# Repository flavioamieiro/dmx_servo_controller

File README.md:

# dmx_servo_controller

AMIEIRO + DELED : SERVO DMX Controller V0.1

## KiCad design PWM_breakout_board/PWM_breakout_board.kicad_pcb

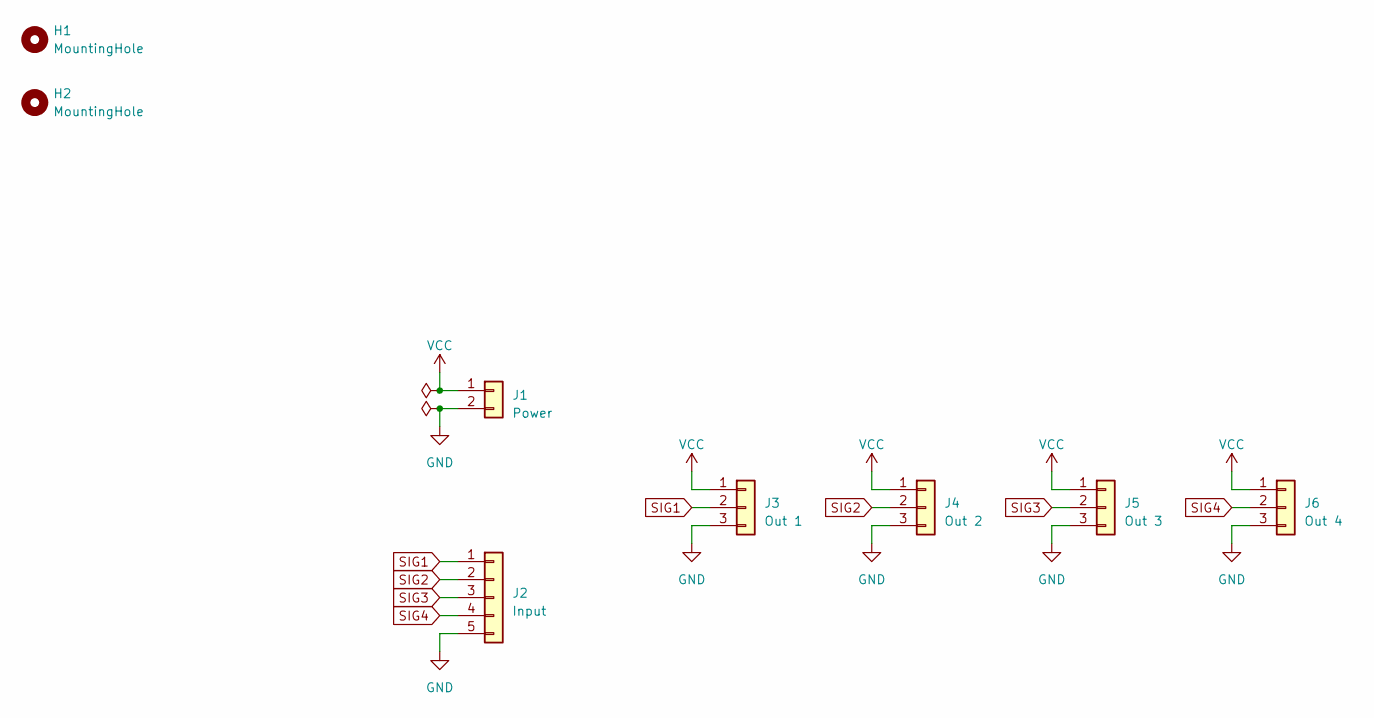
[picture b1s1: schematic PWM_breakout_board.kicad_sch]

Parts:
H1, H2: MountingHole; MountingHole_4.3mm_M4_ISO7380
J1: Power; TerminalBlock_bornier-2_P5.08mm
J2: Input; JST_XH_B5B-XH-AM_1x05_P2.50mm_Vertical
J3: Out 1; TerminalBlock_bornier-3_P5.08mm
J4: Out 2; TerminalBlock_bornier-3_P5.08mm
J5: Out 3; TerminalBlock_bornier-3_P5.08mm
J6: Out 4; TerminalBlock_bornier-3_P5.08mm

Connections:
GND: J1.2, J2.5, J3.3, J4.3, J5.3, J6.3
SIG1: J2.1, J3.2
SIG2: J2.2, J4.2
SIG3: J2.3, J5.2
SIG4: J2.4, J6.2
VCC: J1.1, J3.1, J4.1, J5.1, J6.1

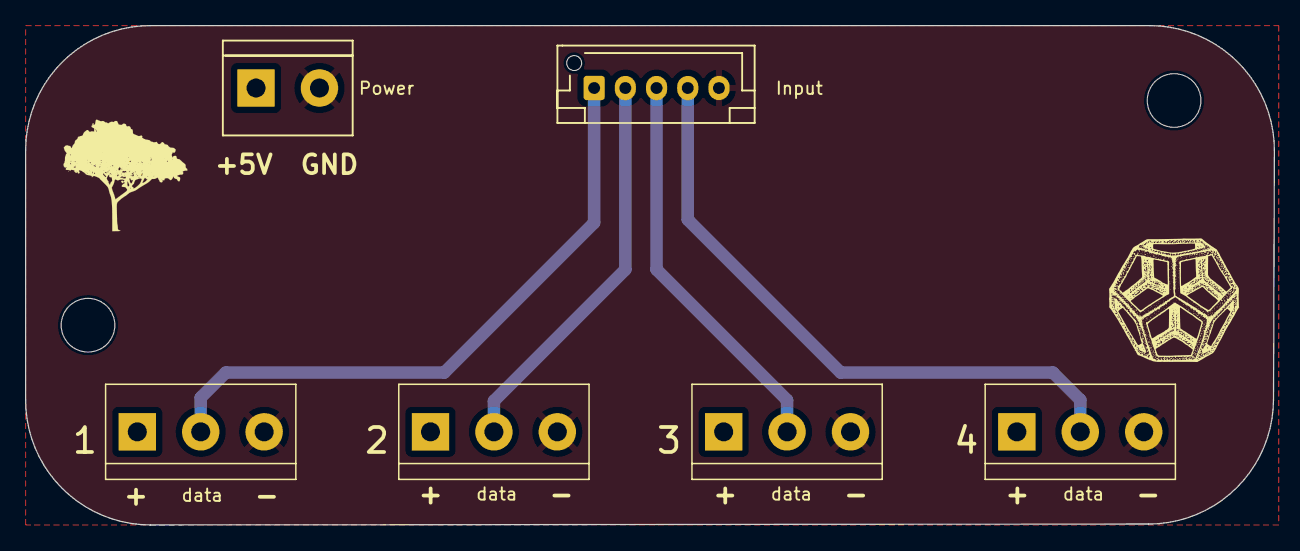
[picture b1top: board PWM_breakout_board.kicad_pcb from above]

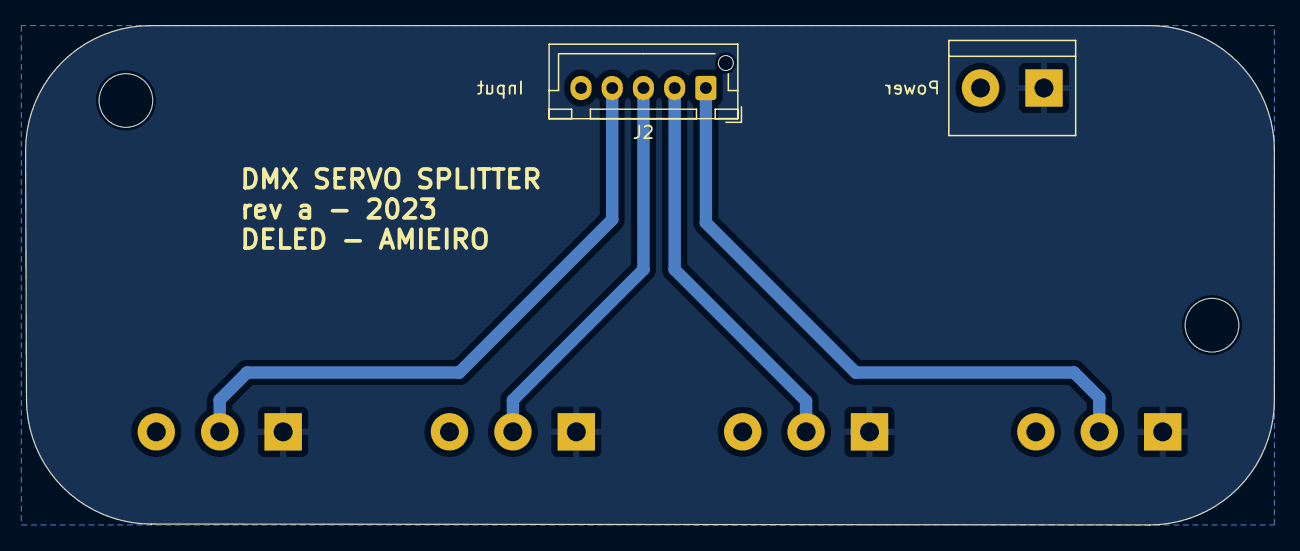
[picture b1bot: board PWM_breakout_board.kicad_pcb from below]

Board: 2 copper layers, 100.0 x 40.0 mm, 9 parts (2 on the bottom side), 6 nets.

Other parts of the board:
Ref**: Val**; ipe_logo_FSilk_10x10

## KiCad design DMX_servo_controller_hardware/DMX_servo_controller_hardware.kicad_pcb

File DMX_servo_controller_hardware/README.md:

DMX servo controller

This source describes Open Hardware and is licensed under the CERN-OHL-S v2.
You may redistribute and modify this source and make products using it under
the terms of the [CERN-OHL-S v2](https://ohwr.org/cern_ohl_s_v2.txt).

Source location: https://github.com/flavioamieiro/Neopixel-Pico-Arcade

As per CERN-OHL-S v2 section 4, should You produce hardware based on this
source, You must where practicable maintain the Source Location visible on the
external case of the Gizmo or other products you make using this source.

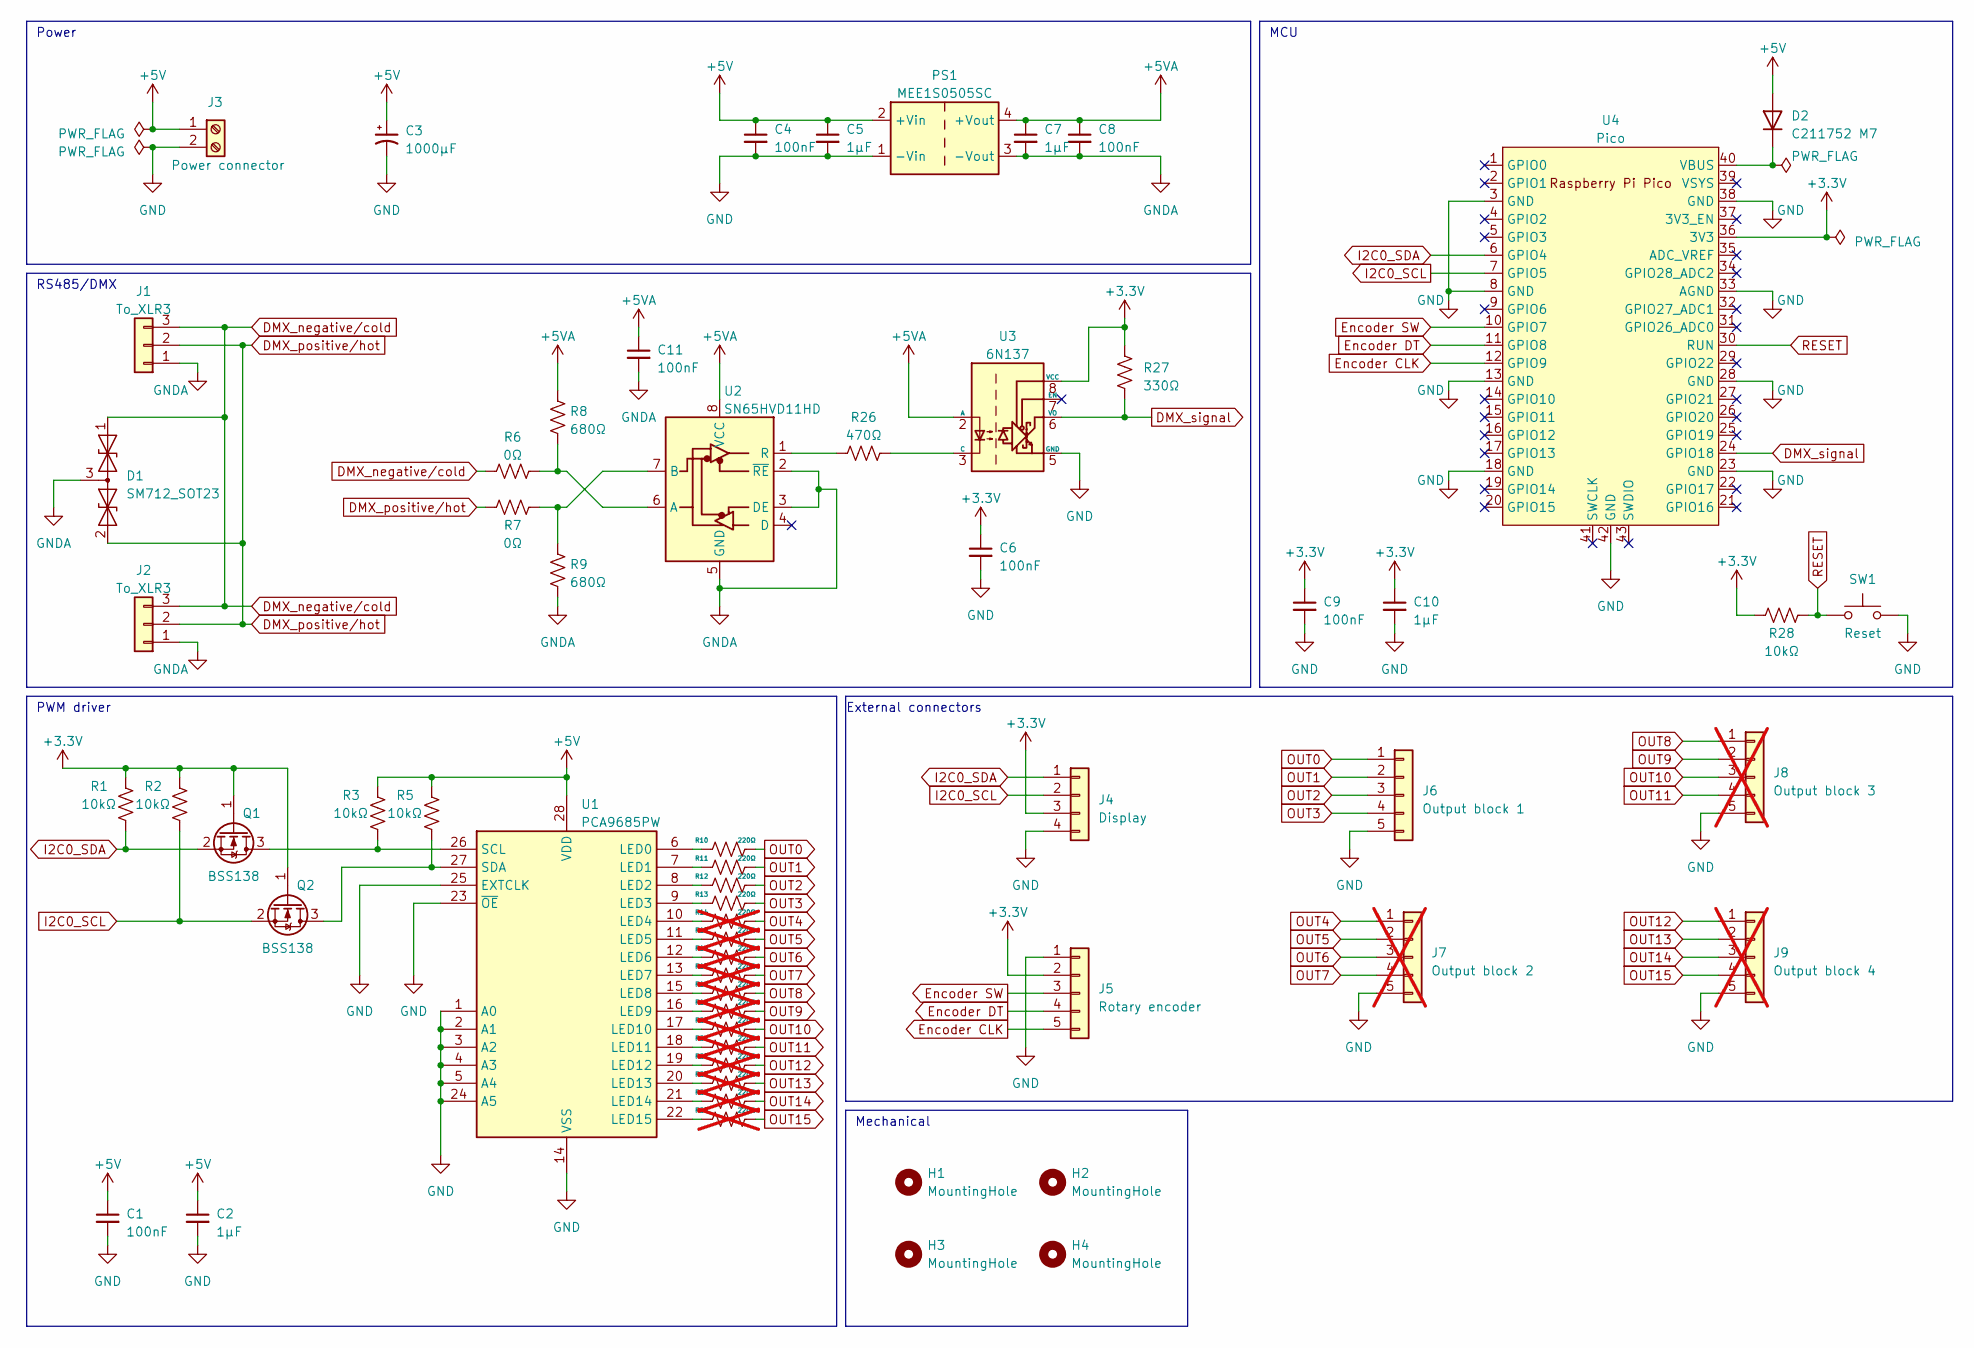
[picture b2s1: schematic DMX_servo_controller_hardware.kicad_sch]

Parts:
C1, C4, C6, C8, C9, C11: 100nF; C_0805_2012Metric_Pad1.18x1.45mm_HandSolder
C2, C5, C7, C10: 1μF; C_0805_2012Metric_Pad1.18x1.45mm_HandSolder
C3: 1000μF; CP_Radial_D10.0mm_P5.00mm
D1: SM712_SOT23; SOT-23
D2: C211752 M7; D_SMA
H1, H2, H3, H4: MountingHole; MountingHole_4.3mm_M4_ISO7380
J1, J2: To_XLR3; JST_XH_B3B-XH-AM_1x03_P2.50mm_Vertical
J3: Power connector; TerminalBlock_bornier-2_P5.08mm
J4: Display; JST_XH_B4B-XH-AM_1x04_P2.50mm_Vertical
J5: Rotary encoder; JST_XH_B5B-XH-AM_1x05_P2.50mm_Vertical
J6: Output block 1; JST_XH_B5B-XH-AM_1x05_P2.50mm_Vertical
J7: Output block 2; JST_XH_B5B-XH-AM_1x05_P2.50mm_Vertical; not fitted
J8: Output block 3; JST_XH_B5B-XH-AM_1x05_P2.50mm_Vertical; not fitted
J9: Output block 4; JST_XH_B5B-XH-AM_1x05_P2.50mm_Vertical; not fitted
PS1: MEE1S0505SC; Converter_DCDC_Murata_MEE1SxxxxSC_THT
Q1, Q2: BSS138; SOT-23
R1, R2, R3, R5, R28: 10kΩ; R_0805_2012Metric_Pad1.20x1.40mm_HandSolder
R6, R7: 0Ω; R_0805_2012Metric_Pad1.20x1.40mm_HandSolder
R8, R9: 680Ω; R_0805_2012Metric_Pad1.20x1.40mm_HandSolder
R10, R11, R12, R13: 220Ω; R_0805_2012Metric_Pad1.20x1.40mm_HandSolder
R14, R15, R16, R17, R18, R19, R20, R21, R22, R23, R24, R25: 220Ω; R_0805_2012Metric_Pad1.20x1.40mm_HandSolder; not fitted
R26: 470Ω; R_0805_2012Metric_Pad1.20x1.40mm_HandSolder
R27: 330Ω; R_0805_2012Metric_Pad1.20x1.40mm_HandSolder
SW1: Reset; SW_SPST_TL3342
U1: PCA9685PW; TSSOP-28_4.4x9.7mm_P0.65mm
U2: SN65HVD11HD; DIP-8_W7.62mm
U3: 6N137; 6N137-X007T
U4: Pico; RPi_Pico_SMD_TH

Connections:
+3.3V: C6.1, C9.1, C10.1, J4.3, J5.2, Q1.1 (G), Q2.1 (G), R1.1, R2.1, R27.1, R28.1, U3.8 (VCC), U4.36 (3V3)
+5V: C1.1, C2.1, C3.1, C4.1, C5.1, D2.2 (A), J3.1, PS1.2 (+Vin), R3.1, R5.1, U1.28 (VDD)
+5VA: C7.1, C8.1, C11.1, PS1.4 (+Vout), R8.1, U2.8 (VCC), U3.2 (A)
DMX_negative/cold: D1.1 (A1), J1.3, J2.3, R6.1
DMX_positive/hot: D1.2 (A2), J1.2, J2.2, R7.1
DMX_signal: R27.2, U3.6 (VO), U4.24 (GPIO18)
Encoder CLK: J5.5, U4.12 (GPIO9)
Encoder DT: J5.4, U4.11 (GPIO8)
Encoder SW: J5.3, U4.10 (GPIO7)
GND: C1.2, C2.2, C3.2, C4.2, C5.2, C6.2, C9.2, C10.2, J3.2, J4.4, J5.1, J6.5, J7.5, J8.5, J9.5, PS1.1 (-Vin), SW1.2, U1.1 (A0), U1.2 (A1), U1.3 (A2), U1.4 (A3), U1.5 (A4), U1.14 (VSS), U1.23 (~OE), U1.24 (A5), U1.25 (EXTCLK), U3.5 (GND), U4.3 (GND), U4.8 (GND), U4.13 (GND), U4.18 (GND), U4.23 (GND), U4.28 (GND), U4.33 (AGND), U4.38 (GND), U4.42 (GND)
GNDA: C7.2, C8.2, C11.2, D1.3 (common), J1.1, J2.1, PS1.3 (-Vout), R9.2, U2.2 (~RE), U2.3 (DE), U2.5 (GND)
I2C0_SCL: J4.2, Q2.2 (S), R2.2, U4.7 (GPIO5)
I2C0_SDA: J4.1, Q1.2 (S), R1.2, U4.6 (GPIO4)
unnamed: D2.1 (K), U4.40 (VBUS)
unnamed: Q1.3 (D), R3.2, U1.26 (SCL)
unnamed: Q2.3 (D), R5.2, U1.27 (SDA)
unnamed: R10.1, U1.6 (LED0)
unnamed: R11.1, U1.7 (LED1)
unnamed: R12.1, U1.8 (LED2)
unnamed: R13.1, U1.9 (LED3)
unnamed: R14.1, U1.10 (LED4)
unnamed: R15.1, U1.11 (LED5)
unnamed: R16.1, U1.12 (LED6)
unnamed: R17.1, U1.13 (LED7)
unnamed: R18.1, U1.15 (LED8)
unnamed: R19.1, U1.16 (LED9)
unnamed: R20.1, U1.17 (LED10)
unnamed: R21.1, U1.18 (LED11)
unnamed: R22.1, U1.19 (LED12)
unnamed: R23.1, U1.20 (LED13)
unnamed: R24.1, U1.21 (LED14)
unnamed: R25.1, U1.22 (LED15)
unnamed: R6.2, R8.2, U2.6 (A)
unnamed: R7.2, R9.1, U2.7 (B)
unnamed: R26.2, U2.1 (R)
unnamed: R26.1, U3.3 (C)
OUT0: J6.1, R10.2
OUT1: J6.2, R11.2
OUT2: J6.3, R12.2
OUT3: J6.4, R13.2
OUT4: J7.1, R14.2
OUT5: J7.2, R15.2
OUT6: J7.3, R16.2
OUT7: J7.4, R17.2
OUT8: J8.1, R18.2
OUT9: J8.2, R19.2
OUT10: J8.3, R20.2
OUT11: J8.4, R21.2
OUT12: J9.1, R22.2
OUT13: J9.2, R23.2
OUT14: J9.3, R24.2
OUT15: J9.4, R25.2
RESET: R28.2, SW1.1, U4.30 (RUN)

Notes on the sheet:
External connectors
PWM driver
RS485/DMX
MCU
Power
Mechanical

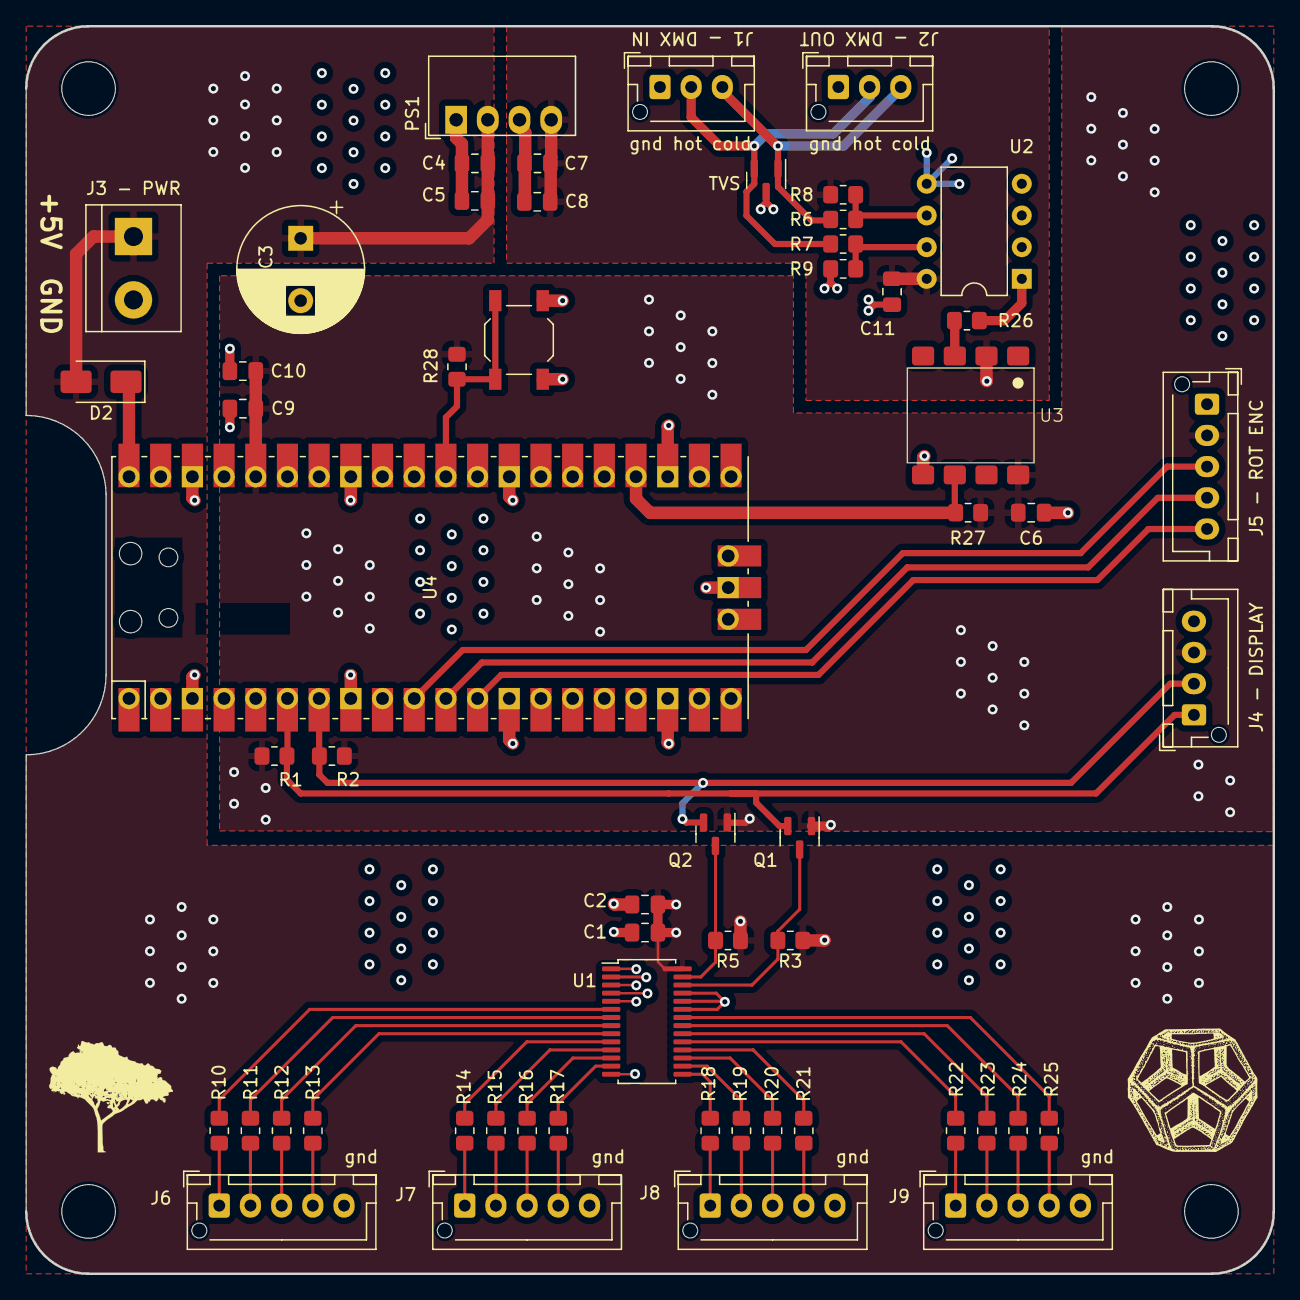
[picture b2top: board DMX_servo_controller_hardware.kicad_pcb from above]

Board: 4 copper layers, 100.0 x 100.0 mm, 62 parts (0 on the bottom side), 53 nets.

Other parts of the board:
Ref**: Val**; ipe_logo_FSilk_10x10

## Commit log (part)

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2023-03-13 Commit inicial
2023-03-13 Adiciona esquemático do protótipo de conexão do RS485
    Essa versão não tem ainda isolamento mas foi a que usamos para receber
    com sucesso mensagens DMX da mesa controladora.
2023-03-15 Adiciona código de exemplo pra ler 3 canais DMX
    Esse código funciona na IDE do Arduino usando o Arduino-pico [1]
    [1]: https://github.com/earlephilhower/arduino-pico
2023-03-15 Adiciona licença para a parte de hardware
2023-03-20 Adds Raspberry Pi pico symbol and footprint from ncarandini/KiCad-RP-Pico
    The footprint and symbol are taken from
    https://github.com/ncarandini/KiCad-RP-Pico which has a license that
    explicitly allows it to be used in projects without the same license.
    This commit also updates project files to Kicad 7.0.1
2023-03-21 Isolates DMX signal from the rest of the electronics
    We're using a 0505 5v DC/DC isolator for power and an 6N137 optocoupler
    for the signal.
    The 6N137 is supposed to work with 5V, but our tests (and other designs)
    showed that 3.3V works fine and means the optocoupler works as a level
    shifter.
2023-03-22 Moves XLR connector to a hierarchical sheet
    The XLR connectors will be in a daughter board that can be used as a
    breakout board for XLR connectors.
2023-03-22 Adds Pi Pico to the schematics
    This also adds a connector for 5V power (a screw terminal that will be
    connected to the external power supply). The 3v3 rail will come from the
    pico's regulator.
2023-03-22 Adds connections for display
    This also fixes the Reset switch (I was missing the signal on the
    push button) and adds an external connector for the XLR signal (In case
    we use the daughter board detached from the main board).
2023-03-22 WIP: Adds PCA9685 PWM driver
    This adds the IC and some minimal circuitry around it, but there's still
    work to be done here.
2023-03-29 Adds pull-up resistors to PCA9685 i2c lines
2023-03-29 Adds external connectors for the servos
2023-03-29 Fixes GND pin 38 type in the pi pico symbol
2023-03-30 FIxes ERC errors
2023-05-02 Renames example code
    Arduino prefers if the sketch is in a directory with the same name.
2023-05-03 Fixes OE and EXT_CLK pins on the PCA9685 schematics
    OE is active low, so it needs to be pulled to ground.
2023-05-03 Uses same i2c bus for display and pwm controller
    The devices have different addresses. There's no good reason for us not
    to use the same bus.
2023-05-03 First code example with most elements integrated
    For now, the code reads DMX input synchronously and sets channels 0 and
    15 to their position based on channel 1.
    Channels 2 and 3 define the min and max (respectively) duty cycle values
    for `setPWM` since at least the servos we tested on seem to not match
    the datasheet.
    The input value for all DMX channels is output on the OLED display.
2023-05-10 Allows controlling servos independently with each DMX channel
    This commit restructures the code to allow each servo to keep it's own
    state. This removes the temporary calibration channels that existed
    for debugging. A calibration wizzard should be included in the UI later.
2023-05-12 DMX_servo_controller_hardware/DMX_servo_controller_hardware-backups/ DMX_servo_controller_hardware/MCU_RaspberryPi_and_Boards.pretty/desktop.ini DMX_servo_controller_hardware/desktop.ini "Defini\303\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
2023-05-13 Powers PCA9685 from 5V rail
    With this, the PWM signal will be on the level the servos expect, since
    they will be powered with the same voltage. The i2c lines are level
    shifted since the RP2040 GPIOs are not 5V tolerant.
2023-05-13 Adds a diode to stop the USB from feeding the power supply when programming
2023-05-13 "addded datasheets and references repositories"
2023-05-13 "removed gdoc from files - added to .gitignore"
2023-05-13 "removed definições e escolhas.gdoc from repo"
2023-05-22 Adds power flag to the VUSB net after the diode
    This is necessary so the ERC will not complain about the pin do being
    driven.
2023-05-22 Adds minimal example code to interface with rotary encoder
    This uses Matthias Hertel's RotaryEncoder library[1].
    [1]: https://github.com/mathertel/RotaryEncoder
2023-05-22 Reorganizes code and fixes bug in servo update reference
    The loop function is now much easier to read and only calls specific
    functions that handle certain subsystems. Also, I don't know how to
    handle pointers.
2023-05-22 Reasigns component designators
2023-05-23 Final review of the schematics
    * Fixes SCL pull-up in PCA9685
    * Reviews pinouts
    * Adds series resistor to PWM signals
    * Adds bulk decoupling capacitor to 5V power rail
2023-05-26 Assigns footprints to some of the components
2023-05-26 Changes schematic to have only header to plug the panel mounted XLR3 connectors
    We will use panel mounted XLR connector, so we don't need the daughter
    board and the PCB XLR connectors anymore. Instead, the external ones
    will connect to the PCB via 2 JST headers.
2023-05-26 Assigns footprint for test points
    We might want to have all test points going to one connector (01x06 pin
    header) to make the layout easier in the future.
2023-05-26 Reorder JST conectors and PCA9685 outputs for completion (OCD) / added DNP in 4out8 outputs / removed unnecessary resistor for upper 8 outputs of PCA9685 testpoints
2023-05-31 Adds #autosaved_files# to .gitignore
2023-05-31 Adds footprint for reset pushbutton
    The footprint almost matches (and is definitely within tolerances) for
    the technical drawing and measurements taken from the pushbuttons to be
    used.
2023-06-01 Uses screw terminals for servo output connectors
2023-06-01 Uses DIP-8 footprint for SN65HVD12
2023-06-01 Switches symbol and footprint for diode on VUSB
    We're using the C211752[1] from yangjie, but since there's no schematic
    symbol for it, I replaced it with the MRA4003T3G since it has the same
    functionality and footprint and changed the value to reflect the correct
    part number.
    [1]: https://datasheet.lcsc.com/lcsc/1912111437_Yangzhou-Yangjie-Elec-Tech-M7_C211752.pdf
2023-06-01 Adds output for all PWM channels
    They are marked as unpopulated, but it's a good idea to route all
    outputs since we can than populate them if we want more channels.
2023-06-02 Reasigns all component designations
    Now that the schematic is closer to the final configuration we can have
    a better distribution of designators.
2023-06-02 Moves DMX input to GPIO15 on the Pico
    GPIO0 is UART_TX, which was causing issues[1].
    [1]: https://github.com/jostlowe/Pico-DMX/issues/26#issuecomment-1573000484
2023-06-02 Reads DMX messages asynchronously
    This way, we don't need to block until a message is sent, so we can
    process input from the rotary encoder even if no controller is sending
    data to the DMX bus.
2023-06-02 Removes minimum delay between servo moves
    Even though we're reading DMX input asynchronously, we're still only
    processing the data once per loop. Our code is already complex enough
    that by the time we loop through again we're already past the threshold
    we were setting.
2023-06-05 Changes PWM output connectors
    The outputs will be broken out into a JST connector (with ground) in
    blocks of 4 that can then be brought to the connectors to be used by the
    end-user. This is a more flexible design, as we can have the break-out
    board placed in a better place in the enclosure and also permits power
    to be delivered directly to the breakout board.
2023-06-05 Assigns footprints to symbols in PWM breakout board schematics
2023-06-05 Adds first draft of breakout board PCB mechanical design
    This is a very rough sketch for now.
2023-06-05 Uses similar 3D model for terminal blocks in the breakout board
    The Phoenix connectors are very similar to ours and the 3d models don't
    have any major impact, so we can use them since the bornier symbols
    don't have one.
2023-06-05 Roughly routes PWM breakout board as a first draft
2023-06-05 Updates PCBnew file
2023-06-05 Fixes 3d model path for PI Pico footprint
2023-06-06 Fixes footprints for resistors in the main schematics
2023-06-06 Sets main board PCB as 4 layers and set some defaults
2023-06-06 Adds four M4 mounting holes to main board
2023-06-06 Fixes decoupling in PCA9685
    When changing the power supply for the IC, I forgot to change the
    decoupling caps.
2023-06-06 Regroups components in PCB
    This is still far from a final positioning, but the groups are more
    coherent now.
2023-06-15 Switches display code to use SSD1306 OLEDs
    The displays we sourced use this controller. Since the code to actually
    interact with the display uses the Adafruit GFX library, the replacement
    is almost drop-in.
2023-07-02 First draft routing of the DMX section of the PCB
    This is far from the final layout, but it might help to start
    visualizing things.
2023-07-02 Repositions rest of the components to route them in an easier way
2023-07-02 Moves DMX signal input to GPIO18
    This will make it much easier to route the board.
2023-07-03 Reassigns pins in the code to match schematics
2023-07-03 First draft route for everything that was unrouted
    There's definitely a lot to improve still, but all nets are connected.
2023-07-14 Edits some of the silkscreen an adjusts positioning slightly
2023-07-14 Reorganizes component positioning/layout
    The connectors are now all close to the edge o the board and grouped by
    function.
    The space between components in the DMX and uC sections was reduced,
    leaving some space to reduce the overall board size later a bit if we
    decide to.
2023-07-14 Fixes DRC warnings
    This commit also hides the silkscreen for all the pins in the Pico.
2023-07-14 Increases trace thickness for DMX signal
2023-07-17 Removes splash screen from code
    Since the DMX read is now async, the splash screen was never shown.
2023-07-17 Via stitching, add C11 decoupling cap (transciever), layout adjusts
2023-07-18 add personal logo + infos into main board, edited F.silk labels into main board, changed dimensions of daughter board + reposition of components, included logo .pretty into project.
2023-07-18 Adds personal logo to the PCB
2023-07-18 Adds recess for USB connector
2023-07-18 Updates footprints in breakout board to fix DRC warnings
2023-07-18 Adds silkscreen to outputs in breakout board
2023-07-26 Finalizes PCB
    * Changes connector descriptions that didn't match schematics
    * Reviews silkscreen
    * Minor layout changes
2023-07-26 Generates gerber files from PCB
2023-07-26 Generates gerber files for splitter
2023-07-26 Adds schematic PDFs
2023-07-26 Adds zip files with generated Gerbers
2023-08-16 Added file for OLED and Rotary Encoder menu Handling Created barebones example for debuging DMX comm
2023-08-18 Added "building menu" folder with code to integrate menu building and dmx input
2023-08-18 added comments in code for future work
2023-08-24 Building menu.ino file organization + Added pioasm.exe builder for PIO
2023-08-24 Added new file for in software for memory handling: RP2040_flash for example and menu_with_memory for later integration
2023-08-25 Adds very simple (and untested) implementation of servo min value setting
    This allows the change of the min_pos value of each servo, which should
    take effect immediately.
    Note: the values are not yet saved to flash
    The code has a lot of duplication and should probably be refactored
    later.
2023-08-25 Adds simple (and untested) implementation for setting servo max values
    All the caveates from the implementation (in the last commit) of min
    values apply here also.
2023-08-25 Cleans whitespace
2023-08-25 alteration in menu_with_memory - WIP
2023-08-28 Revert "alteration in menu_with_memory - WIP"
    This reverts commit fc7660216aca39dfabe0624e600f1e978795dfe0.
2023-08-28 Fixes Servo_limits menu return going back to main menu -> now going to servo menu, as expected
2023-08-28 Adds working example of read/write using the EEPROM library
2023-09-01 Added PCA9685 datasheet to repo
2023-09-18 Version 1.1
2024-01-28 ADDED V1.2 of firmware implementation, servo limit range in menu quick fix
